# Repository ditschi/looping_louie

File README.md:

# Looping Louie Wi-Fi upgrade

Retrofit electronics for **Looping Louie** (old and new edition) and **Loopin' Chewie**. The board goes into the
**battery compartment without soldering** and makes the game controllable from a **web UI on your phone**, with
game modes, custom modes, game master and player roles. The original lever keeps working as start/stop.

*Main board (46 × 14.1 mm, AA format, 4 layers): ESP32-C6 module on the left, motor driver and power path in the
middle, USB-C on the right. Rendered from the current KiCad layout (`just images`).*

| Exploded | Assembled |
|---|---|
|  |  |

*The real board (KiCad 3D export) in the 3D-printed AA sleeve: shell, two end caps, filament dowels (red). Nickel
strips from the bottom pads make the battery contacts. The board registers in the slots of the end caps; the
envelope check `just hull` confirms it stays inside the AA diameter.*

## Status

> 2026-11-11 · second version, nothing ordered yet. The main board is rev B (low-Iq LDO TPS7A2633 for 3.3 V),
> the design to order; rev A with the SPX3819 LDO is kept as a fallback under the Git tag `rev-a-spx3819`.

| Part | State |
|---|---|
| Concept | done ([hardware](docs/hardware-concept.md), [software](docs/software-concept.md), [web UI](docs/web-ui-concept.md)) |
| Main board | schematic done, routed (own router), ERC/DRC 0, 0 unconnected; rev B with the LDO TPS7A2633 (VSYS 3.0–6.6 V, standby approx. 15–18 µA), datasheet delta review done ([main-board-c6.md](docs/main-board-c6.md)) |
| Charger board | schematic and layout done, ERC/DRC clean ([charger-board.md](docs/charger-board.md)) |
| 3D-printed parts | AA sleeve, C-cell adapter and charger holder modelled; checked against the current layout (`just hull`) |
| Firmware | Rust, step 0 written (bring-up and test probes), builds, not yet run on a board ([firmware/louie-fw](firmware/louie-fw/README.md)) |
| Web UI | clickable prototype ([web/poc](web/poc/README.md)) |

The old MicroPython/ESP8266 version is in the tag `v1-legacy`.

## Components

| Assembly | Description |
|---|---|
| **Main board** | AA cell format, 4 layers, components on one side: ESP32-C6-MINI-1 (Wi-Fi, BLE), DRV8213 H-bridge with current sensing, USB-C for flashing and 5 V operation, supply for 1S Li-ion up to 4 × AA, lever detection; solder pads on the bottom for player inputs, LEDs, I²C |
| **Charger board** | also AA format: USB-C (charging), charge controller, LiPo connection. Sits upright in the second compartment (replaces the bridge there) or is glued into the base |
| **Bridge** | copper AA dummy for the second compartment when the charger board sits in the base |
| **AA sleeve / C-cell adapter** | 3D-printed shell with end caps that holds the main board in the AA compartment; an extra sleeve makes it fit the C-cell compartment of the old Louie ([hardware/mechanics](hardware/mechanics/README.md)) |
| **Firmware** | Rust (std on ESP-IDF); game logic as a hardware-independent crate that runs on the ESP, in PC tests and as WebAssembly in the browser (mode preview) |
| **Web UI** | served offline by the ESP; concept and clickable prototype in `web/poc` |

## Documentation

- Hardware: [hardware concept](docs/hardware-concept.md), [main board](docs/main-board-c6.md),
  [charger board](docs/charger-board.md) (with wiring diagram), [3D-printed parts](hardware/mechanics/README.md)
- Software: [firmware architecture](docs/firmware-architecture.md), [software concept](docs/software-concept.md),
  [web UI concept](docs/web-ui-concept.md), [mode builder](docs/mode-builder.md), [device pairing](docs/device-pairing.md)
- Test setup before the board exists: [test hardware](docs/test-hardware.md)
- Development workflow (tools, generators, router, routing score): [development](docs/development.md),
  [routing score](docs/routing-score.md), [code health](docs/code-health.md) (score, commit gate, hardware checks)
- Open items and decisions: [open items](docs/open-items.md), [decision history](docs/decision-history.md),
  [concept review 2026-11-10](docs/review-2026-11-10.md), [supply proposal: buck converter](docs/proposal-supply-buck.md),
  [supply proposal: standby with Li-ion](docs/proposal-supply-standby.md),
  [wiring review](docs/wiring-review.md)
- Costs: [cost estimate](docs/cost-estimate.md)
- Ideas and studies: [ideas](docs/ideas.md), [optional hardware](docs/idea-optional-hardware.md),
  [wireless buttons](docs/idea-wireless-buttons.md), [power bank](docs/idea-power-bank.md),
  [Zigbee](docs/idea-zigbee-operation.md), [wireless controllers](docs/analysis-wireless-controllers.md)

## Directories

```
docs/                 concepts, decisions, development guide, images (docs/images/)
hardware/
  bom/parts.csv       BOM with manufacturer parts, LCSC numbers, alternatives
  lib/                project library (symbols, footprints, 3D models) – created with just parts
  main-board/         KiCad project of the main board (4 layers)
  charger-board/      KiCad project of the charger board (2 layers)
  mechanics/          3D-printed parts (OpenSCAD): main board sleeve, charger board holder
  scripts/            generators (schematic, layout, placement), router with keep-best gate,
                      routing score, envelope check, part fetching, tool check
  routing-score.toml  weights of the routing score
web/
  poc/                clickable web UI prototype (one HTML file, offline)
  prototype/          first, outdated UI draft
firmware/louie-fw/    Rust firmware (ESP-IDF), step 0: bring-up and test probes
tools/                downloaded tools (Freerouting, pre-router), created by setup.sh, not in Git
AGENTS.md             orientation and validation for coding agents
justfile              all development commands (just --list)
setup.sh              installs all tools
```

## Quick start

```bash
./setup.sh     # install all tools (once, Ubuntu/Debian)
just check     # check the tools
just --list    # all commands
```

Common commands:

```bash
just images    # board renders, copper layers, schematic, sleeve assembly → docs/images/
just model     # 3D model of the board (STEP, GLB, STL) → build/main-board/3d/
just hull      # check the board against the AA sleeve
just stl       # 3D-print files and previews → build/mechanics/
just fab       # Gerber, drill, CPL and BOM for fabrication → build/main-board/fab/
```

Setup and workflow in detail: [docs/development.md](docs/development.md)

## License

Using, building and adapting the project is free for **non-commercial purposes**; making money with the project
requires prior permission. Software: [PolyForm Noncommercial 1.0.0](LICENSES/PolyForm-Noncommercial-1.0.0.md),
hardware and docs: [CC BY-NC-SA 4.0](LICENSES/CC-BY-NC-SA-4.0.txt). Details and exceptions: [LICENSE](LICENSE).

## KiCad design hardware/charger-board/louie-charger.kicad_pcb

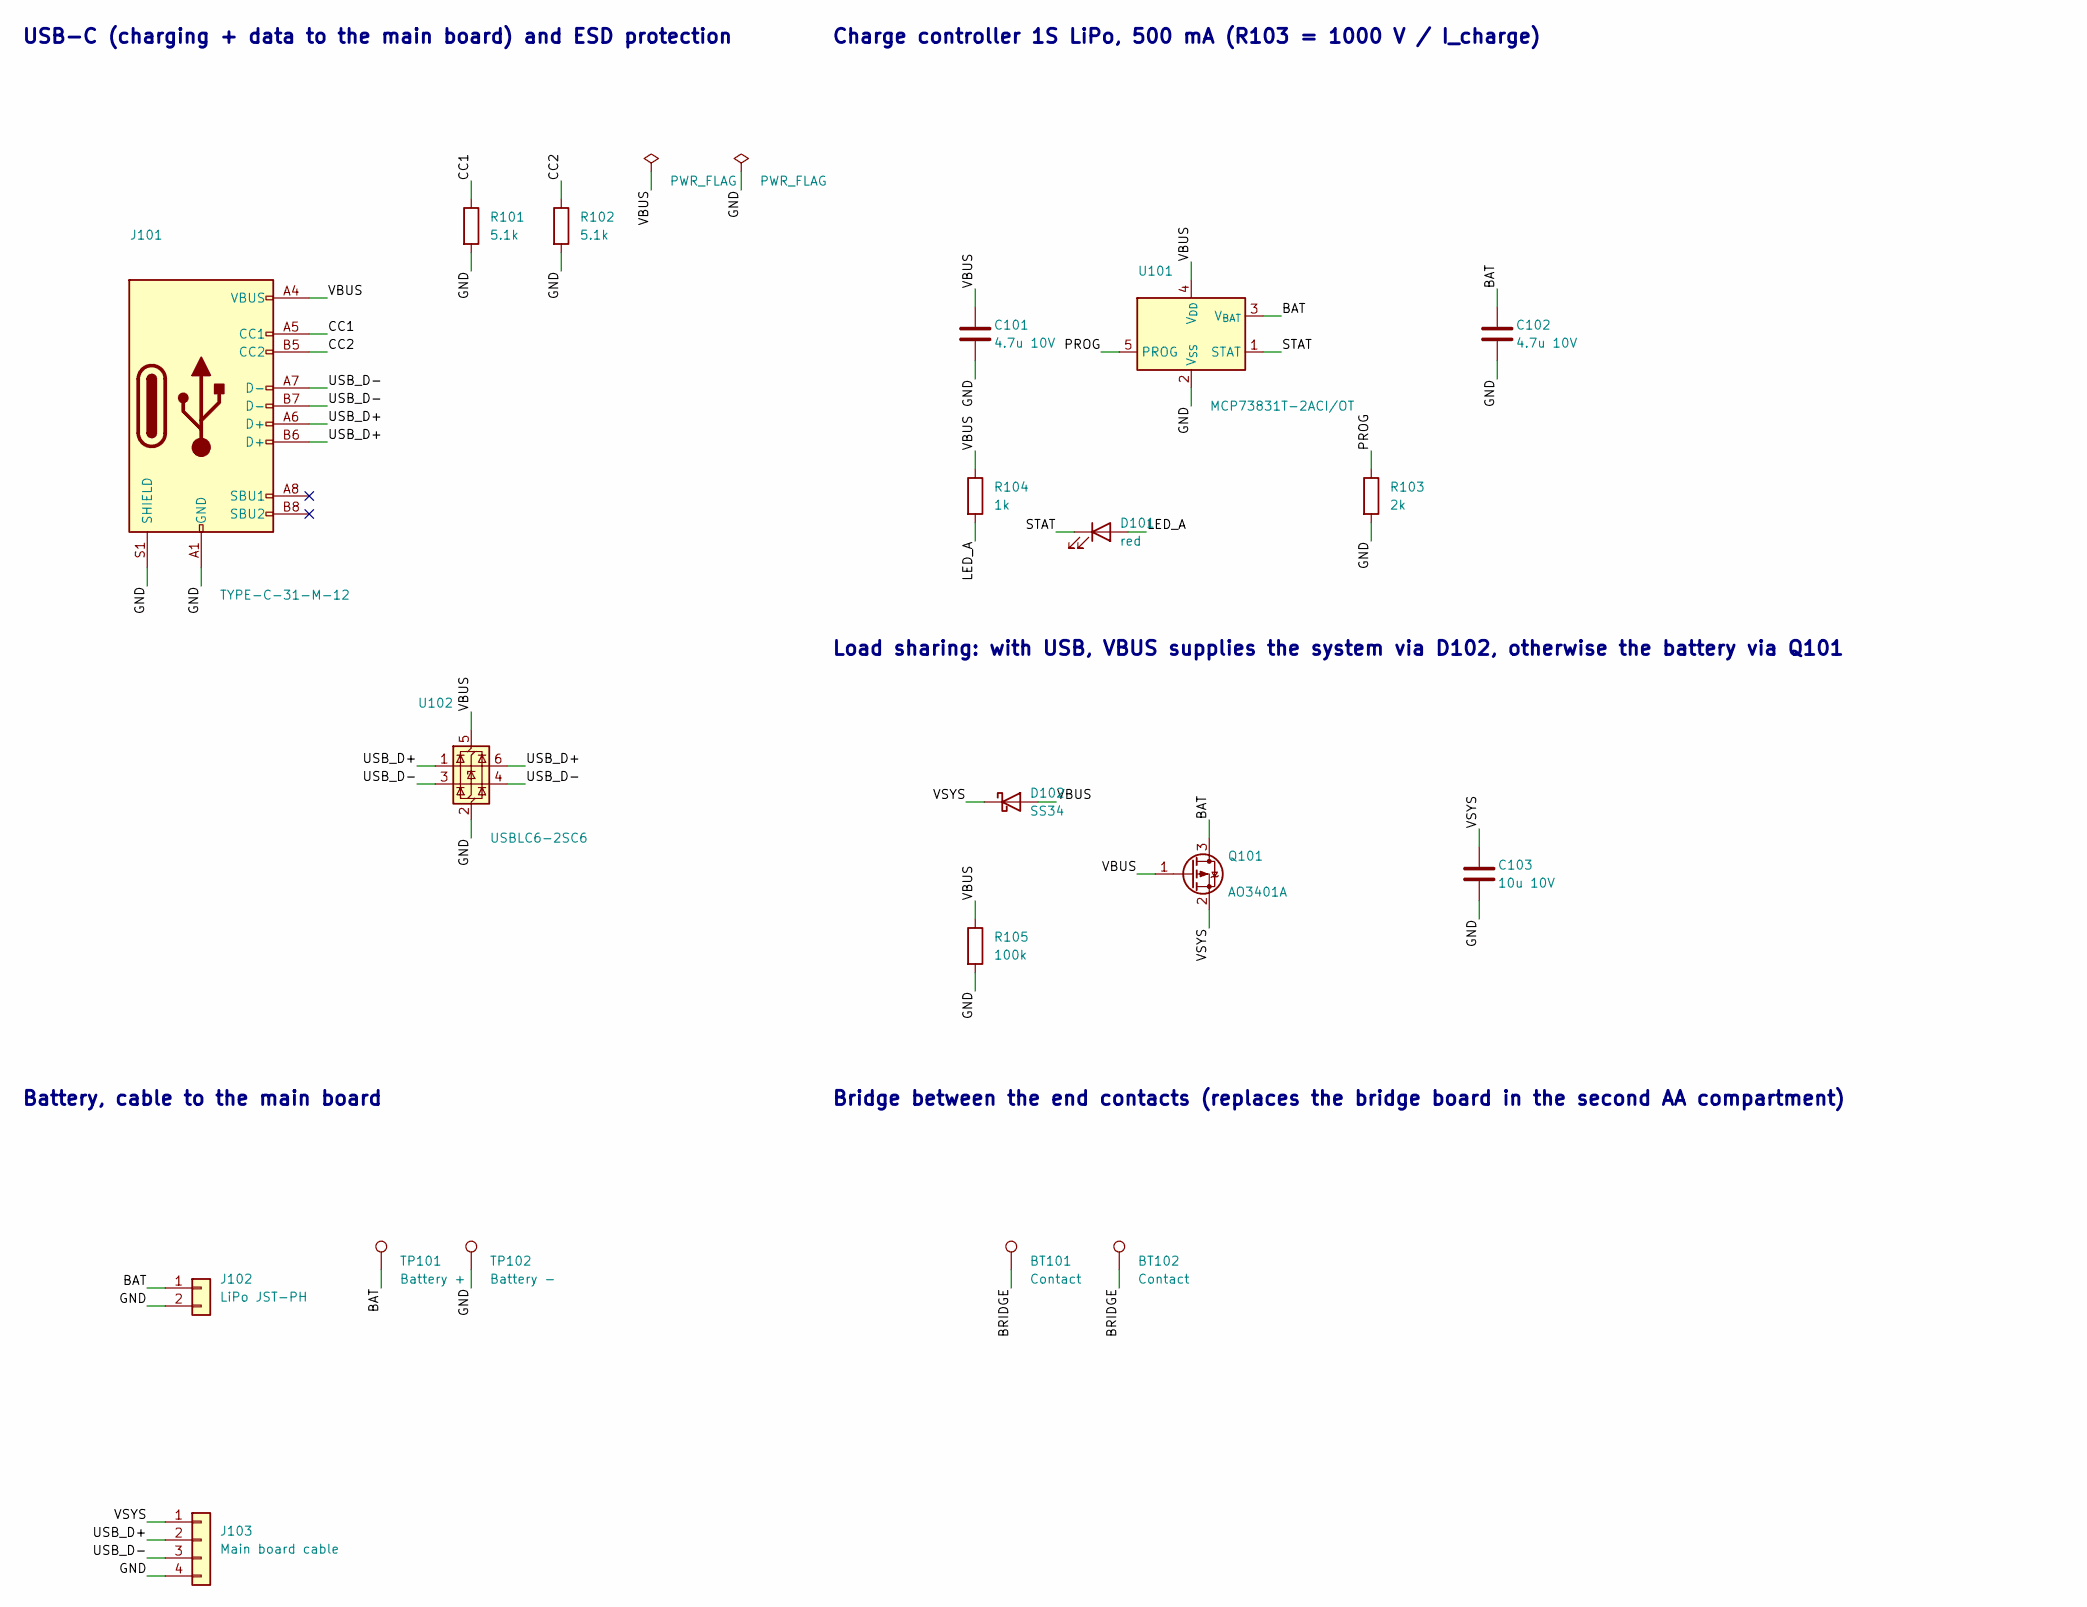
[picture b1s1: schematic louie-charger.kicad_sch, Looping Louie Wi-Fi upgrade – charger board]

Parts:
BT101, BT102: Contact; TestPoint_Pad_2.0x2.0mm
C101, C102: 4.7u 10V; C_0603_1608Metric
C103: 10u 10V; C_0805_2012Metric
D101: red; LED_0603_1608Metric; LCSC Part C2286
D102: SS34; D_SMA; LCSC Part C8678
J101: TYPE-C-31-M-12; USB_C_Receptacle_HRO_TYPE-C-31-M-12; LCSC Part C165948
J102: LiPo JST-PH; JST_PH_S2B-PH-SM4-TB_1x02-1MP_P2.00mm_Horizontal; LCSC Part C295747
J103: Main board cable; SolderPads_1x04_P2.00mm
Q101: AO3401A; SOT-23; LCSC Part C15127
R101, R102: 5.1k; R_0603_1608Metric
R103: 2k; R_0603_1608Metric
R104: 1k; R_0603_1608Metric
R105: 100k; R_0603_1608Metric
TP101: Battery +; TestPoint_Pad_2.0x2.0mm
TP102: Battery -; TestPoint_Pad_2.0x2.0mm
U101: MCP73831T-2ACI/OT; SOT-23-5; LCSC Part C424093
U102: USBLC6-2SC6; SOT-23-6; LCSC Part C7519

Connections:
/BAT: C102.1, J102.1, Q101.3 (D), TP101.1, U101.3 (V_{BAT})
/BRIDGE: BT101.1, BT102.1
/CC1: J101.A5 (CC1), R101.1
/CC2: J101.B5 (CC2), R102.1
/GND: C101.2, C102.2, C103.2, J101.A1 (GND), J101.A12 (GND), J101.B1 (GND), J101.B12 (GND), J101.S1 (SHIELD), J102.2, J103.4, R101.2, R102.2, R103.2, R105.2, TP102.1, U101.2 (V_{SS}), U102.2 (GND)
/LED_A: D101.2 (A), R104.2
/PROG: R103.1, U101.5 (PROG)
/STAT: D101.1 (K), U101.1 (STAT)
/USB_D+: J101.A6 (D+), J101.B6 (D+), J103.2, U102.1 (I/O1), U102.6 (I/O1)
/USB_D-: J101.A7 (D-), J101.B7 (D-), J103.3, U102.3 (I/O2), U102.4 (I/O2)
/VBUS: C101.1, D102.2 (A), J101.A4 (VBUS), J101.A9 (VBUS), J101.B4 (VBUS), J101.B9 (VBUS), Q101.1 (G), R104.1, R105.1, U101.4 (V_{DD}), U102.5 (VBUS)
/VSYS: C103.1, D102.1 (K), J103.1, Q101.2 (S)

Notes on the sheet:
USB-C (charging + data to the main board) and ESD protection
Charge controller 1S LiPo, 500 mA (R103 = 1000 V / I_charge)
Load sharing: with USB, VBUS supplies the system via D102, otherwise the battery via Q101
Battery, cable to the main board
Bridge between the end contacts (replaces the bridge board in the second AA compartment)

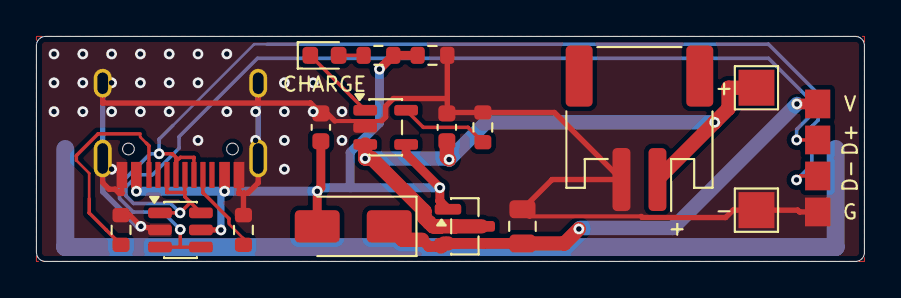
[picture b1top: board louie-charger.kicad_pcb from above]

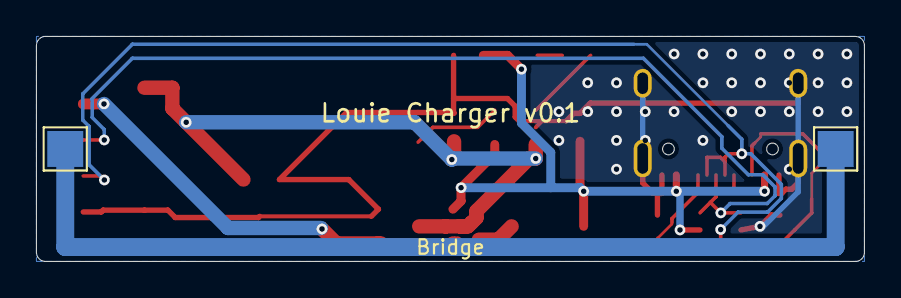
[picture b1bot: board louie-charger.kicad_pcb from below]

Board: 2 copper layers, 46.0 x 12.5 mm, 20 parts (2 on the bottom side), 12 nets.

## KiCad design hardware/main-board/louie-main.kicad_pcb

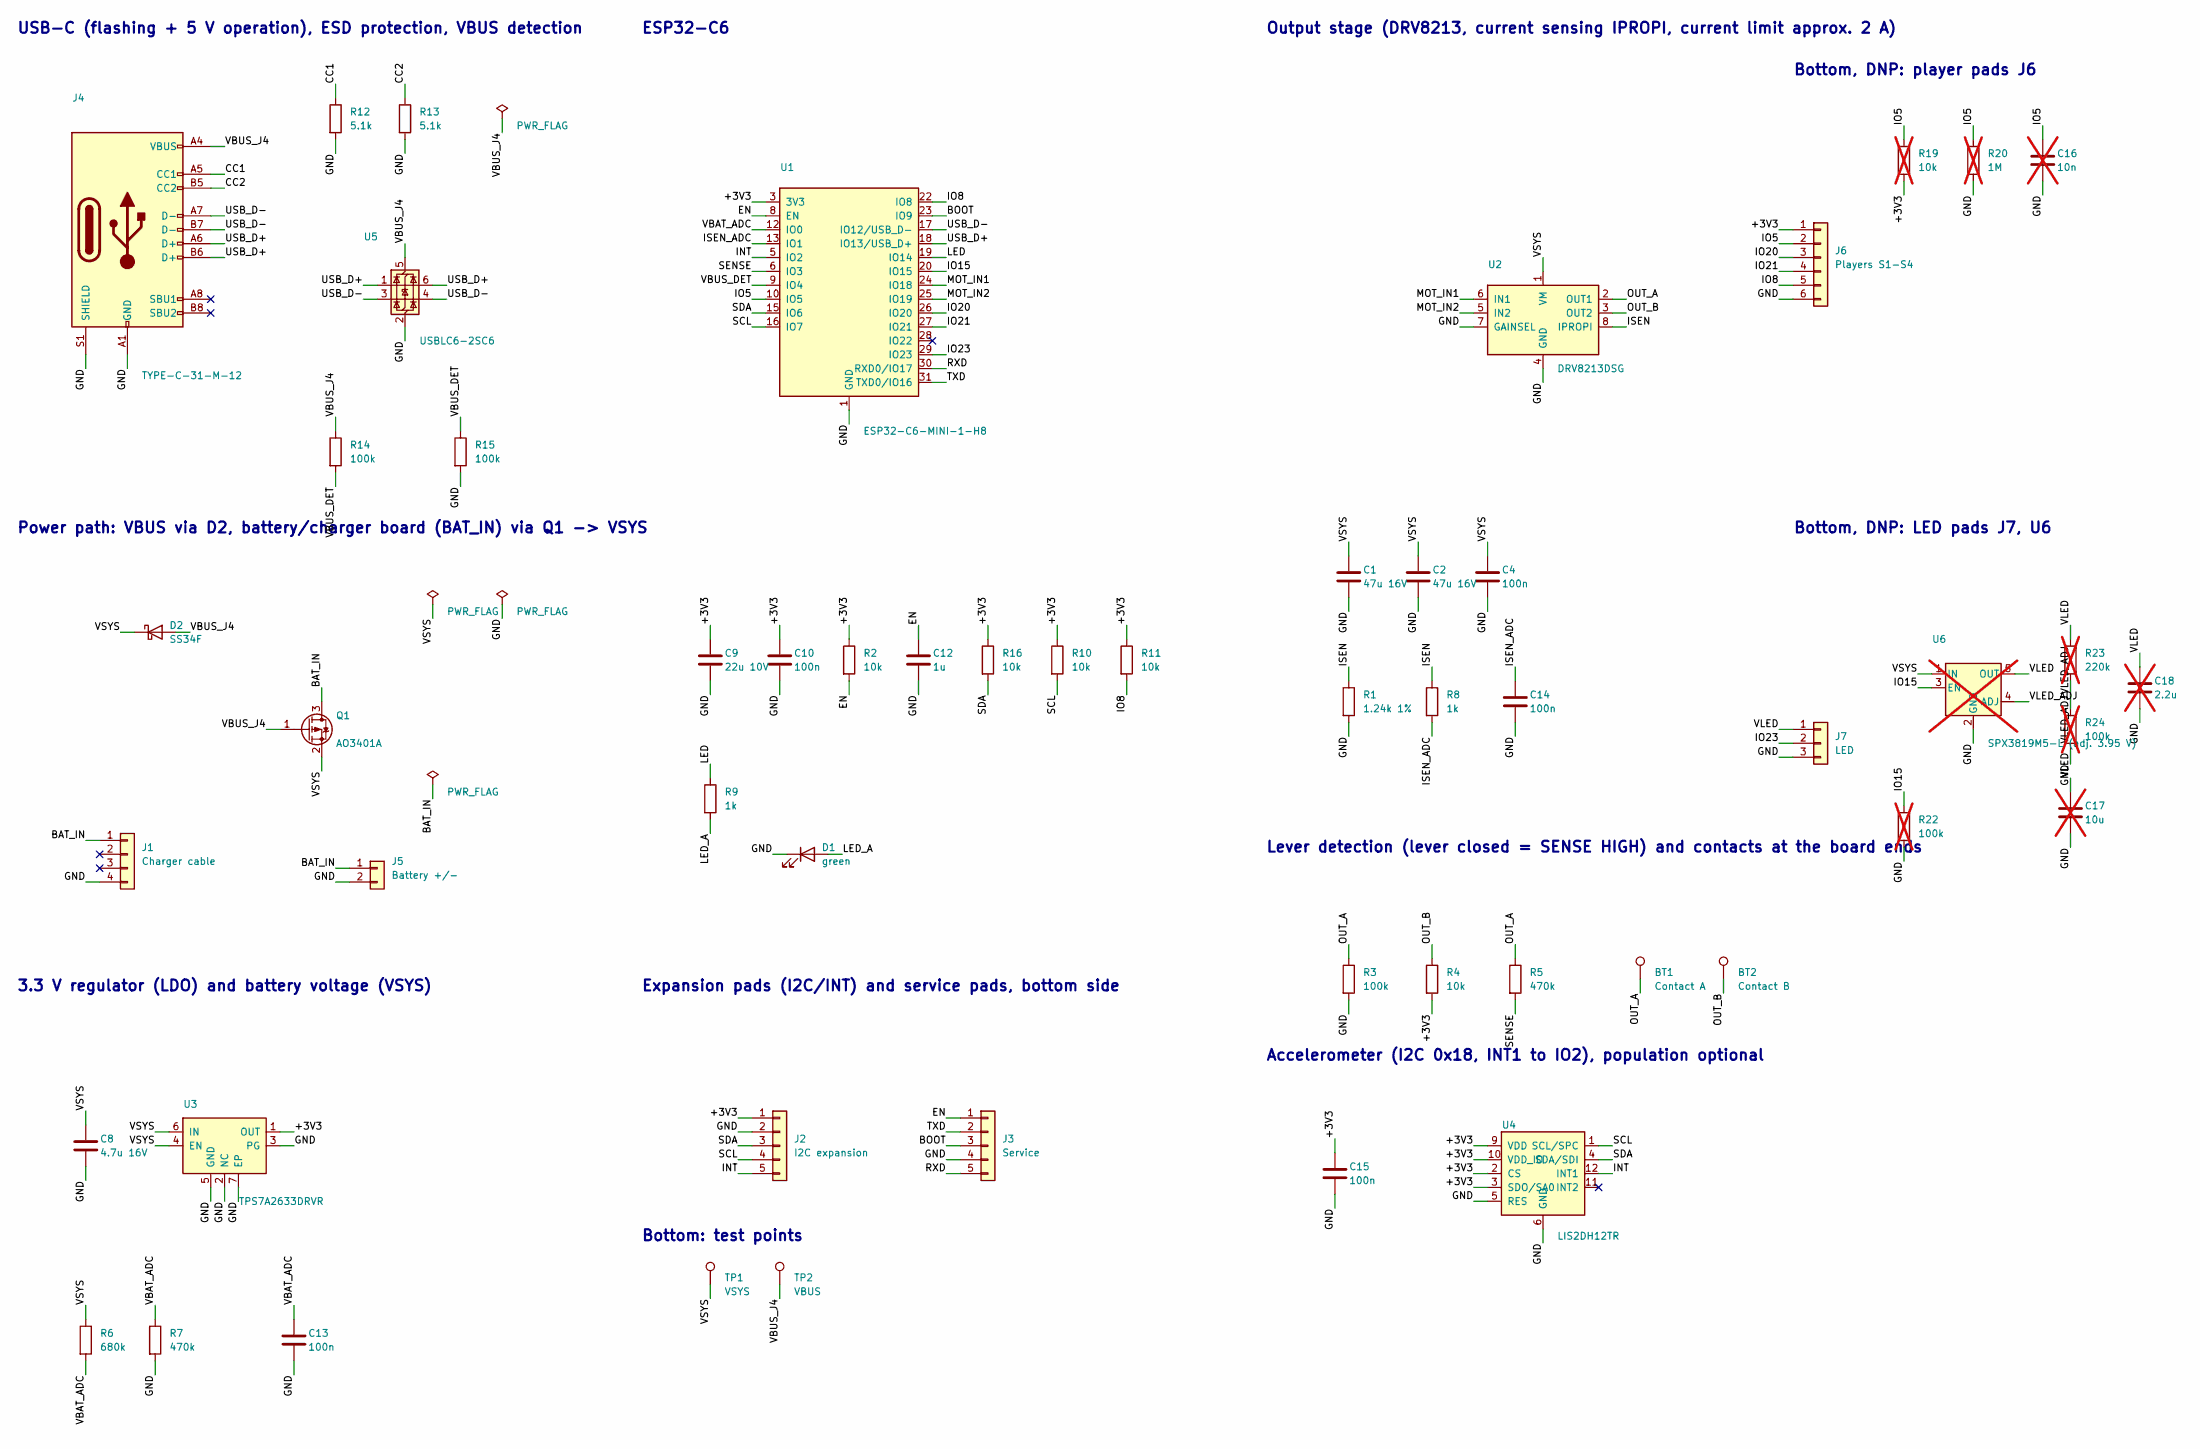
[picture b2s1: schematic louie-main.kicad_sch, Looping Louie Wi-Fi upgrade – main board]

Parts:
BT1: Contact A; TestPoint_Pad_2.0x2.0mm
BT2: Contact B; TestPoint_Pad_2.0x2.0mm
C1, C2: 47u 16V; C_1206_3216Metric
C4, C10, C13, C14, C15: 100n; C_0402_1005Metric
C8: 4.7u 16V; C_0402_1005Metric
C9: 22u 10V; C_0805_2012Metric
C12: 1u; C_0402_1005Metric
C16: 10n; C_0402_1005Metric; LCSC Part C15195; not fitted
C17: 10u; C_0805_2012Metric; LCSC Part C1713; not fitted
C18: 2.2u; C_0402_1005Metric; not fitted
D1: green; LED_0402_1005Metric
D2: SS34F; SMAF_L3.5-W2.6-LS4.7-RD; LCSC Part C60396
J1: Charger cable; SolderPads_1x04_P2.00mm
J2: I2C expansion; SolderPads_1x05_P2.54mm
J3: Service; SolderPads_1x05_P2.54mm
J4: TYPE-C-31-M-12; USB_C_Receptacle_HRO_TYPE-C-31-M-12; LCSC Part C165948
J5: Battery +/-; SolderPads_1x02_2.5x3.5mm
J6: Players S1-S4; SolderPads_1x06_P2.00mm
J7: LED; SolderPads_1x03_P2.54mm
Q1: AO3401A; SOT-23; LCSC Part C15127
R1: 1.24k 1%; R_0402_1005Metric
R2, R4, R10, R11, R16: 10k; R_0402_1005Metric
R3, R14, R15: 100k; R_0402_1005Metric
R5, R7: 470k; R_0402_1005Metric
R6: 680k; R_0402_1005Metric
R8, R9: 1k; R_0402_1005Metric
R12, R13: 5.1k; R_0402_1005Metric
R19: 10k; R_0402_1005Metric; LCSC Part C25744; not fitted
R20: 1M; R_0402_1005Metric; not fitted
R22: 100k; R_0402_1005Metric; LCSC Part C25741; not fitted
R23: 220k; R_0402_1005Metric; not fitted
R24: 100k; R_0402_1005Metric; not fitted
TP1: VSYS; TestPad_D1.0mm
TP2: VBUS; TestPad_D1.0mm
U1: ESP32-C6-MINI-1-H8; WIFIM-SMD_ESP32-C6-MINI-1; LCSC Part C42403058
U2: DRV8213DSG; WSON-8-1EP_2x2mm_P0.5mm_EP0.9x1.6mm; LCSC Part C22407186
U3: TPS7A2633DRVR; WSON-6-1EP_2x2mm_P0.65mm_EP1x1.6mm; LCSC Part C2876256
U4: LIS2DH12TR; LGA-12_2x2mm_P0.5mm; LCSC Part C110926
U5: USBLC6-2SC6; SOT-23-6; LCSC Part C7519
U6: SPX3819M5-L (adj. 3.95 V); SOT-23-5; not fitted

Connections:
/+3V3: C9.1, C10.1, C15.1, J2.1, J6.1, R2.1, R4.2, R10.1, R11.1, R16.1, R19.2, U1.3 (3V3), U3.1 (OUT), U4.2 (CS), U4.3 (SDO/SA0), U4.9 (VDD), U4.10 (VDD_IO)
/BAT_IN: J1.1, J5.1, Q1.3 (D)
/BOOT: J3.3, U1.23 (IO9)
/CC1: J4.A5 (CC1), R12.1
/CC2: J4.B5 (CC2), R13.1
/EN: C12.1, J3.1, R2.2, U1.8 (EN)
/GND: C1.2, C2.2, C4.2, C8.2, C9.2, C10.2, C12.2, C13.2, C14.2, C15.2, C16.2, C17.2, C18.2, D1.1 (K), J1.4, J2.2, J3.4, J4.A1 (GND), J4.A12 (GND), J4.B1 (GND), J4.B12 (GND), J4.S1 (SHIELD), J5.2, J6.6, J7.3, R1.2, R3.2, R7.2, R12.2, R13.2, R15.2, R20.2, R22.2, R24.2, U1.1 (GND), U1.2 (GND), U1.11 (GND), U1.14 (GND), U1.36 (GND), U1.37 (GND), U1.38 (GND), U1.39 (GND), U1.40 (GND), U1.41 (GND), U1.42 (GND), U1.43 (GND), U1.44 (GND), U1.45 (GND), U1.46 (GND), U1.47 (GND), U1.48 (GND), U1.49 (GND), U1.50 (GND), U1.51 (GND), U1.52 (GND), U1.53 (GND), U2.4 (GND), U2.7 (GAINSEL), U2.9 (GND), U3.2 (NC), U3.3 (PG), U3.5 (GND), U3.7 (EP), U4.5 (RES), U4.6 (GND), U4.7 (GND), U4.8 (GND), U5.2 (GND), U6.2 (GND)
/INT: J2.5, U1.5 (IO2), U4.12 (INT1)
/IO5: C16.1, J6.2, R19.1, R20.1, U1.10 (IO5)
/IO8: J6.5, R11.2, U1.22 (IO8)
/IO15: R22.1, U1.20 (IO15), U6.3 (EN)
/IO20: J6.3, U1.26 (IO20)
/IO21: J6.4, U1.27 (IO21)
/IO23: J7.2, U1.29 (IO23)
/ISEN: R1.1, R8.1, U2.8 (IPROPI)
/ISEN_ADC: C14.1, R8.2, U1.13 (IO1)
/LED: R9.1, U1.19 (IO14)
/LED_A: D1.2 (A), R9.2
/MOT_IN1: U1.24 (IO18), U2.6 (IN1)
/MOT_IN2: U1.25 (IO19), U2.5 (IN2)
/OUT_A: BT1.1, R3.1, R5.1, U2.2 (OUT1)
/OUT_B: BT2.1, R4.1, U2.3 (OUT2)
/RXD: J3.5, U1.30 (RXD0/IO17)
/SCL: J2.4, R10.2, U1.16 (IO7), U4.1 (SCL/SPC)
/SDA: J2.3, R16.2, U1.15 (IO6), U4.4 (SDA/SDI)
/SENSE: R5.2, U1.6 (IO3)
/TXD: J3.2, U1.31 (TXD0/IO16)
/USB_D+: J4.A6 (D+), J4.B6 (D+), U1.18 (IO13/USB_D+), U5.1 (I/O1), U5.6 (I/O1)
/USB_D-: J4.A7 (D-), J4.B7 (D-), U1.17 (IO12/USB_D-), U5.3 (I/O2), U5.4 (I/O2)
/VBAT_ADC: C13.1, R6.2, R7.1, U1.12 (IO0)
/VBUS_DET: R14.2, R15.1, U1.9 (IO4)
/VBUS_J4: D2.2 (A), J4.A4 (VBUS), J4.A9 (VBUS), J4.B4 (VBUS), J4.B9 (VBUS), Q1.1 (G), R14.1, TP2.1, U5.5 (VBUS)
/VLED: C17.1, C18.1, J7.1, R23.1, U6.5 (OUT)
/VLED_ADJ: R23.2, R24.1, U6.4 (ADJ)
/VSYS: C1.1, C2.1, C4.1, C8.1, D2.1 (K), Q1.2 (S), R6.1, TP1.1, U2.1 (VM), U3.4 (EN), U3.6 (IN), U6.1 (IN)

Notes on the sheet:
USB-C (flashing + 5 V operation), ESD protection, VBUS detection
Power path: VBUS via D2, battery/charger board (BAT_IN) via Q1 -> VSYS
3.3 V regulator (LDO) and battery voltage (VSYS)
ESP32-C6
Output stage (DRV8213, current sensing IPROPI, current limit approx. 2 A)
Lever detection (lever closed = SENSE HIGH) and contacts at the board ends
Expansion pads (I2C/INT) and service pads, bottom side
Accelerometer (I2C 0x18, INT1 to IO2), population optional
Bottom, DNP: player pads J6
Bottom, DNP: LED pads J7, U6
Bottom: test points

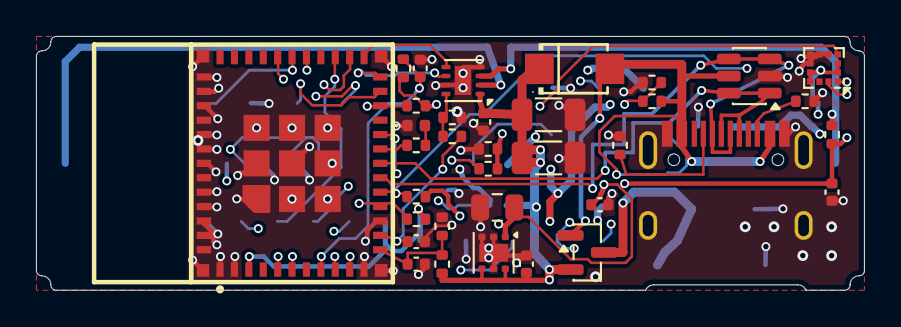
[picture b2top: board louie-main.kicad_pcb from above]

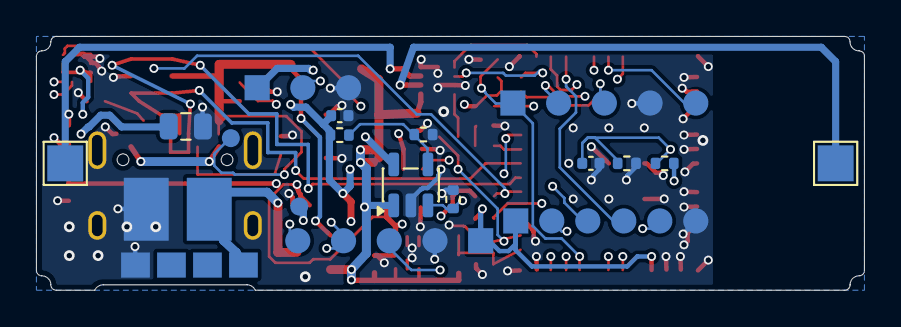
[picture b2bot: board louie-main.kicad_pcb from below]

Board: 4 copper layers, 46.0 x 14.1 mm, 54 parts (19 on the bottom side), 35 nets.

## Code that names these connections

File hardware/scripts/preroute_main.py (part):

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
def preroute_supply(board, fps):
    """VSYS main track in advance (0.5 mm): cathode of Schottky D2 -> C1 -> C2 (vertical at the left
    pads), branch C1 -> C4 -> VM pin 1 of the DRV8213. The rest of VSYS (Q1, LDO, divider) and BAT_IN/VBUS
    are routed by Freerouting in the Power net class."""

    def at(ref, num):
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

def preroute_outputs(board, driver, contact_a, contact_b):
    """Outputs of the DRV8213 in advance: OUT1 (pin 2, OUT_A) and OUT2 (pin 3, OUT_B) each with a 0.3 mm stub to a
    via, on the bottom with 0.4 mm along the -y edge: OUT_A to the left under module and antenna (edge strip) to
    end contact BT1, OUT_B to the right to end contact BT2. Expects rotation 180° (pins 1–4 point to +x)."""
    assert round(driver.GetOrientationDegrees()) % 360 == 180, "preroute_outputs expects rotation 180°"
    pa, pb = pad_of(driver, "2").GetPosition(), pad_of(driver, "3").GetPosition()
    out_a, out_b = pad_of(driver, "2").GetNet(), pad_of(driver, "3").GetNet()
    edge_y = mm(ORIGIN[1] - EDGE_TRACK_Y)
    # OUT_A: via right of the pin, on the bottom diagonally under the driver to the edge, then to the left
    va = (pa.x + mm(1.15), pa.y)
    add_track(board, out_a, (pcbnew.F_Cu, STUB_TRACK), (pa.x, pa.y), va)
    add_via(board, out_a, *va)
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        (ca.x, edge_y + mm(0.8)),
        (ca.x, ca.y),
    )
    # OUT_B: stub diagonally to the lower right (past GND pin 4), via, on the bottom along the edge to the right
    vb = (pb.x + mm(1.7), pb.y - mm(0.4))
    add_track(
        board, out_b, (pcbnew.F_Cu, STUB_TRACK), (pb.x, pb.y), (pb.x + mm(0.6), pb.y), (pb.x + mm(1.0), vb[1]), vb
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

def preroute_led_ldo(board, fps):
    """LED LDO U6 (bottom, DNP): VIN (pin 1) with 0.4 mm on B.Cu straight to the battery VSYS track at x = 4.67, which
    runs 1.5 mm to its right; route_fix.py did not find this short path (variant test 2026-11-10)."""
    pad = pad_of(fps["U6"], "1")
    q = pad.GetPosition()
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def preroute_adc_stubs(board, fps):
    """Short analog connections at the right module pins, locked so that no fanout via or foreign track takes the
    0.7 mm gap between the module pads and the 0402 row (variant test 2026-11-08, docs/main-board-c6.md 11):
    pad 12 (VBAT_ADC) -> C13, pad 13 (ISEN_ADC) -> C14, C13 -> R6 pin 2 above C13 pin 2 (GND), R6 pin 2 -> R7 pin 1.
    Replaces the former VBAT_ADC escape via at the old R6 place."""

    def q(ref, num):
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
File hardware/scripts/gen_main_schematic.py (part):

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        # Flow-through (ST DS4260 Rev 5, Fig. 1/7/18): I/O1 = pins 1 and 6, I/O2 = pins 3 and 4 are each
        # the same node. The line comes from J4 to pin 1/3 and continues under the package to pin 6/4
        # towards the module (no branch/stub).
        pins={"1": "USB_D+", "6": "USB_D+", "3": "USB_D-", "4": "USB_D-", "5": "VBUS_J4", "2": "GND"},
    ),
    # VBUS_DET: divider 100k/100k to IO4 (5 V -> 2.5 V), also gate pull-down of Q1, discharges VBUS
    R("R14", "100k", ("VBUS_J4", "VBUS_DET"), at=(83.82, 101.6)),
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        lcsc="C60396",
        fp="lcsc:SMAF_L3.5-W2.6-LS4.7-RD",
        at=(50.8, 134.62),
        pins={"2": "VBUS_J4", "1": "VSYS"},
    ),
    # Gate to VBUS: with USB, Q1 blocks (no charging of the cell from VBUS), without USB it conducts (gate via
    # R14+R15 to GND). Body diode BAT_IN -> VSYS; cell reversed -> Q1 blocks (reverse polarity protection).
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        at=(78.74, 152.4),
        ref_at=(5.08, -2.54),
        val_at=(5.08, 2.54),
        pins={"1": "VBUS_J4", "2": "VSYS", "3": "BAT_IN"},
    ),
    # Bottom side: cable to the charger board (1 BAT_IN, 4 GND; 2/3 free) and battery pads (cell direct)
    dict(
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        fp="louie:SolderPads_1x04_P2.00mm",
        bom=False,  # solder pads for stranded wires, not populated
        # Only BAT_IN and GND: flashing exclusively via J4 (client decision). Pads 2/3 stay without
        # a net so that the cable pinout of charger board v0.1 (1 VSYS, 2 D+, 3 D-, 4 GND) fits
        at=(45.72, 175.26),
        pins={"1": "BAT_IN", "4": "GND"},
    ),
    dict(
        ref="J5",
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        fp="louie:SolderPads_1x02_2.5x3.5mm",
        bom=False,
        at=(91.44, 177.8),
        pins={"1": "BAT_IN", "2": "GND"},
    ),
    FLAG(1, "VSYS", (101.6, 129.54)),
    FLAG(2, "GND", (114.3, 129.54)),
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        at=(63.5, 228.6),
        ref_at=(-7.62, -7.62),
        val_at=(2.54, 10.16),
        pins={"6": "VSYS", "4": "VSYS", "1": "+3V3", "3": "GND", "5": "GND", "2": "GND", "7": "GND"},
    ),
    C("C8", "4.7u 16V", ("VSYS", "GND"), at=(38.1, 228.6)),
    # --- Battery voltage: 680k/470k, VSYS up to 6.6 V (4 x AA fresh) -> 2.7 V (C6 ADC up to 3.3 V) --------
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        value="green",
        fp="LED_SMD:LED_0402_1005Metric",
        at=(170.18, 175.26),
        pins={"2": "LED_A", "1": "GND"},
    ),
    # Bottom side: solder pads at 2.54 mm pitch (pin header/cable), not populated
    dict(
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        bom=False,
        fp="louie:SolderPads_1x03_P2.54mm",
        at=(355.6, 154.94),
        pins={"1": "VLED", "2": "IO23", "3": "GND"},
    ),
    # SPX3819 adjustable (EN V_IH 2.0 V): VOUT = 1.235 V × (1 + R23/R24) = 3.95 V. At 3.95 V the V5 LED types need
    # V_IH 0.63 × 3.95 = 2.49 V, below the guaranteed ESP32 V_OH (2.64 V); at 5.0 V (3.15 V) the 3.3 V data line
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            at=(383.54, 144.78),
            ref_at=(-7.62, -8.89),
            val_at=(2.54, 10.16),
            pins={"1": "VSYS", "2": "GND", "3": "IO15", "4": "VLED_ADJ", "5": "VLED"},
        )
    ),
    DNP(R("R23", "220k", ("VLED", "VLED_ADJ"), at=(401.32, 139.7))),
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
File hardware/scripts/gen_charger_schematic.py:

#!/usr/bin/env python3
"""Generates the charger board schematic from the circuit description below.

The charger board has the format of the main board (AA) and replaces the bridge in the second AA compartment:
USB-C (horizontal, the plug comes from above across the cell axis), charge controller MCP73831 with load sharing
(play while charging), ESD protection, charge indicator, battery connection, cable solder pads to the main board and
a copper bridge between the end contacts. Alternatively it is glued into the base.

Usage (via just):  just charger-schematic

Warning: overwrites hardware/charger-board/louie-charger.kicad_sch.
"""

import gen_main_schematic as base
from gen_main_schematic import FLAG, TP, TP_CONTACT, C, R

SCH = base.HARDWARE / "charger-board" / "louie-charger.kicad_sch"
R0603 = "Resistor_SMD:R_0603_1608Metric"
C0603 = "Capacitor_SMD:C_0603_1608Metric"
C0805 = "Capacitor_SMD:C_0805_2012Metric"


def R6(*args, **extra):
    return R(*args, fp=R0603, **extra)


BLOCKS = [
    ("USB-C (charging + data to the main board) and ESD protection", (25.4, 25.4)),
    ("Charge controller 1S LiPo, 500 mA (R103 = 1000 V / I_charge)", (139.7, 25.4)),
    ("Load sharing: with USB, VBUS supplies the system via D102, otherwise the battery via Q101", (139.7, 111.76)),
    ("Battery, cable to the main board", (25.4, 175.26)),
    ("Bridge between the end contacts (replaces the bridge board in the second AA compartment)", (139.7, 175.26)),
]

PARTS = [
    # --- USB-C ---------------------------------------------------------------------------------
    dict(
        ref="J101",
        lib="Connector:USB_C_Receptacle_USB2.0_16P",
        value="TYPE-C-31-M-12",
        lcsc="C165948",
        fp="Connector_USB:USB_C_Receptacle_HRO_TYPE-C-31-M-12",
        at=(50.8, 76.2),
        ref_at=(-10.16, -24.13),
        val_at=(2.54, 26.67),
        pins={
            "A4": "VBUS",
            "A9": "VBUS",
            "B4": "VBUS",
            "B9": "VBUS",
            "A5": "CC1",
            "B5": "CC2",
            "A6": "USB_D+",
            "B6": "USB_D+",
            "A7": "USB_D-",
            "B7": "USB_D-",
            "A1": "GND",
            "A12": "GND",
            "B1": "GND",
            "B12": "GND",
            "S1": "GND",
        },
    ),
    # 5.1 k at CC1/CC2: device (sink), every USB-C power supply then delivers 5 V
    R6("R101", "5.1k", ("CC1", "GND"), at=(88.9, 50.8)),
    R6("R102", "5.1k", ("CC2", "GND"), at=(101.6, 50.8)),
    dict(
        ref="U102",
        lib="Power_Protection:USBLC6-2SC6",
        value="USBLC6-2SC6",
        lcsc="C7519",
        fp="Package_TO_SOT_SMD:SOT-23-6",
        at=(88.9, 127),
        ref_at=(-7.62, -8.89),
        val_at=(2.54, 10.16),
        pins={"1": "USB_D+", "6": "USB_D+", "3": "USB_D-", "4": "USB_D-", "5": "VBUS", "2": "GND"},
    ),
    FLAG(1, "VBUS", (114.3, 43.18)),
    FLAG(2, "GND", (127, 43.18)),
    # --- Charge controller ----------------------------------------------------------------------
    dict(
        ref="U101",
        lib="Battery_Management:MCP73831-2-OT",
        value="MCP73831T-2ACI/OT",
        lcsc="C424093",
        fp="Package_TO_SOT_SMD:SOT-23-5",
        at=(190.5, 66.04),
        ref_at=(-7.62, -8.89),
        val_at=(2.54, 10.16),
        pins={"4": "VBUS", "2": "GND", "3": "BAT", "5": "PROG", "1": "STAT"},
    ),
    C("C101", "4.7u 10V", ("VBUS", "GND"), at=(160.02, 66.04), fp=C0603),
    C("C102", "4.7u 10V", ("BAT", "GND"), at=(233.68, 66.04), fp=C0603),
    R6("R103", "2k", ("PROG", "GND"), at=(215.9, 88.9)),
    # charge indicator: STAT pulls to GND while charging -> LED on; full or without USB -> off
    R6("R104", "1k", ("VBUS", "LED_A"), at=(160.02, 88.9)),
    dict(
        ref="D101",
        lib="Device:LED",
        value="red",
        lcsc="C2286",
        fp="LED_SMD:LED_0603_1608Metric",
        at=(177.8, 93.98),
        pins={"2": "LED_A", "1": "STAT"},
    ),
    # --- Load sharing (Microchip AN1149) -------------------------------------------------------
    dict(
        ref="Q101",
        lib="Transistor_FET:AO3401A",
        value="AO3401A",
        lcsc="C15127",
        fp="Package_TO_SOT_SMD:SOT-23",
        at=(190.5, 142.24),
        ref_at=(5.08, -2.54),
        val_at=(5.08, 2.54),
        pins={"1": "VBUS", "2": "VSYS", "3": "BAT"},
    ),
    dict(
        ref="D102",
        lib="Device:D_Schottky",
        value="SS34",
        lcsc="C8678",
        fp="Diode_SMD:D_SMA",
        at=(165.1, 132.08),
        pins={"2": "VBUS", "1": "VSYS"},
    ),
    R6("R105", "100k", ("VBUS", "GND"), at=(160.02, 152.4)),  # pulls the gate to GND without USB -> Q101 conducts
    C("C103", "10u 10V", ("VSYS", "GND"), at=(231.14, 142.24), fp=C0805),
    # --- Battery and cable ---------------------------------------------------------------------
    dict(
        ref="J102",
        lib="Connector_Generic:Conn_01x02",
        value="LiPo JST-PH",
        lcsc="C295747",
        fp="Connector_JST:JST_PH_S2B-PH-SM4-TB_1x02-1MP_P2.00mm_Horizontal",
        at=(50.8, 200.66),
        pins={"1": "BAT", "2": "GND"},
    ),
    TP("TP101", "Battery +", "BAT", at=(76.2, 198.12), fp=TP_CONTACT),  # solder pads instead of connector
    TP("TP102", "Battery -", "GND", at=(88.9, 198.12), fp=TP_CONTACT),
    dict(
        ref="J103",
        lib="Connector_Generic:Conn_01x04",
        value="Main board cable",
        fp="louie:SolderPads_1x04_P2.00mm",
        bom=False,  # same pinout as J1 of the main board
        at=(50.8, 236.22),
        pins={"1": "VSYS", "2": "USB_D+", "3": "USB_D-", "4": "GND"},
    ),
    # --- Bridge --------------------------------------------------------------------------------
    TP("BT101", "Contact", "BRIDGE", at=(165.1, 198.12), fp=TP_CONTACT),
    TP("BT102", "Contact", "BRIDGE", at=(180.34, 198.12), fp=TP_CONTACT),
]


if __name__ == "__main__":
    base.main(
        base.Sheet(
            path=SCH,
            parts=PARTS,
            blocks=BLOCKS,
            title="Looping Louie Wi-Fi upgrade – charger board",
            comment="AA format (compartment 2 instead of the bridge) or glued into the base, see docs/charger-board.md",
            project="louie-charger",
            generator="gen_charger_schematic.py",
        )
    )

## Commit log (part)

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2018-09-30 Added startup script boot.py
2018-09-30 initial main.py allowing to control the onboard LED
2021-10-03 current unstaged work
2021-10-03 wip -- reworked game and hw_control
2023-02-10 current work before switching to esp32 config
2023-02-10 boot.py now working - hardware/Led.py - hardware/wifi.py
2023-02-13 Timers, LED and morotr abstraction now working
2023-02-13 Timers, LED and motor abstraction now working
2023-02-13 added Fritzing pcb
2023-11-07 Bump flake8 from 6.0.0 to 6.1.0
    Bumps [flake8](https://github.com/pycqa/flake8) from 6.0.0 to 6.1.0.
    - [Commits](https://github.com/pycqa/flake8/compare/6.0.0...6.1.0)
    ---
    updated-dependencies:
    - dependency-name: flake8
    dependency-type: direct:development
2023-11-07 current work
2023-11-07 updating pipenv
2023-11-13 Bump black from 22.12.0 to 23.11.0
    Bumps [black](https://github.com/psf/black) from 22.12.0 to 23.11.0.
    - [Release notes](https://github.com/psf/black/releases)
    - [Changelog](https://github.com/psf/black/blob/main/CHANGES.md)
    - [Commits](https://github.com/psf/black/compare/22.12.0...23.11.0)
    ---
    updated-dependencies:
2023-11-13 Bump gitpython from 3.1.31 to 3.1.37
    Bumps [gitpython](https://github.com/gitpython-developers/GitPython) from 3.1.31 to 3.1.37.
    - [Release notes](https://github.com/gitpython-developers/GitPython/releases)
    - [Changelog](https://github.com/gitpython-developers/GitPython/blob/main/CHANGES)
    - [Commits](https://github.com/gitpython-developers/GitPython/compare/3.1.31...3.1.37)
    ---
    updated-dependencies:
2023-11-29 Bump cryptography from 41.0.5 to 41.0.6
    Bumps [cryptography](https://github.com/pyca/cryptography) from 41.0.5 to 41.0.6.
    - [Changelog](https://github.com/pyca/cryptography/blob/main/CHANGELOG.rst)
    - [Commits](https://github.com/pyca/cryptography/compare/41.0.5...41.0.6)
    ---
    updated-dependencies:
    - dependency-name: cryptography
2023-12-11 Bump pylint from 3.0.2 to 3.0.3
    Bumps [pylint](https://github.com/pylint-dev/pylint) from 3.0.2 to 3.0.3.
    - [Release notes](https://github.com/pylint-dev/pylint/releases)
    - [Commits](https://github.com/pylint-dev/pylint/compare/v3.0.2...v3.0.3)
    ---
    updated-dependencies:
    - dependency-name: pylint
2023-12-18 Bump black from 23.11.0 to 23.12.0
    Bumps [black](https://github.com/psf/black) from 23.11.0 to 23.12.0.
    - [Release notes](https://github.com/psf/black/releases)
    - [Changelog](https://github.com/psf/black/blob/main/CHANGES.md)
    - [Commits](https://github.com/psf/black/compare/23.11.0...23.12.0)
    ---
    updated-dependencies:
2023-12-25 Bump black from 23.11.0 to 23.12.1
    Bumps [black](https://github.com/psf/black) from 23.11.0 to 23.12.1.
    - [Release notes](https://github.com/psf/black/releases)
    - [Changelog](https://github.com/psf/black/blob/main/CHANGES.md)
    - [Commits](https://github.com/psf/black/compare/23.11.0...23.12.1)
    ---
    updated-dependencies:
2024-01-01 Bump pytest from 7.4.3 to 7.4.4
    Bumps [pytest](https://github.com/pytest-dev/pytest) from 7.4.3 to 7.4.4.
    - [Release notes](https://github.com/pytest-dev/pytest/releases)
    - [Changelog](https://github.com/pytest-dev/pytest/blob/main/CHANGELOG.rst)
    - [Commits](https://github.com/pytest-dev/pytest/compare/7.4.3...7.4.4)
    ---
    updated-dependencies:
2024-01-08 Bump flake8 from 6.1.0 to 7.0.0
    Bumps [flake8](https://github.com/pycqa/flake8) from 6.1.0 to 7.0.0.
    - [Commits](https://github.com/pycqa/flake8/compare/6.1.0...7.0.0)
    ---
    updated-dependencies:
    - dependency-name: flake8
    dependency-type: direct:development
2024-01-10 Bump gitpython from 3.1.37 to 3.1.41
    Bumps [gitpython](https://github.com/gitpython-developers/GitPython) from 3.1.37 to 3.1.41.
    - [Release notes](https://github.com/gitpython-developers/GitPython/releases)
    - [Changelog](https://github.com/gitpython-developers/GitPython/blob/main/CHANGES)
    - [Commits](https://github.com/gitpython-developers/GitPython/compare/3.1.37...3.1.41)
    ---
    updated-dependencies:
2024-01-11 Bump jinja2 from 3.1.2 to 3.1.3
    Bumps [jinja2](https://github.com/pallets/jinja) from 3.1.2 to 3.1.3.
    - [Release notes](https://github.com/pallets/jinja/releases)
    - [Changelog](https://github.com/pallets/jinja/blob/main/CHANGES.rst)
    - [Commits](https://github.com/pallets/jinja/compare/3.1.2...3.1.3)
    ---
    updated-dependencies:
2024-01-29 Bump black from 23.12.1 to 24.1.1
    Bumps [black](https://github.com/psf/black) from 23.12.1 to 24.1.1.
    - [Release notes](https://github.com/psf/black/releases)
    - [Changelog](https://github.com/psf/black/blob/main/CHANGES.md)
    - [Commits](https://github.com/psf/black/compare/23.12.1...24.1.1)
    ---
    updated-dependencies:
2024-01-29 Bump pytest from 7.4.3 to 8.0.0
    Bumps [pytest](https://github.com/pytest-dev/pytest) from 7.4.3 to 8.0.0.
    - [Release notes](https://github.com/pytest-dev/pytest/releases)
    - [Changelog](https://github.com/pytest-dev/pytest/blob/main/CHANGELOG.rst)
    - [Commits](https://github.com/pytest-dev/pytest/compare/7.4.3...8.0.0)
    ---
    updated-dependencies:
2024-02-06 Bump cryptography from 41.0.6 to 42.0.0
    Bumps [cryptography](https://github.com/pyca/cryptography) from 41.0.6 to 42.0.0.
    - [Changelog](https://github.com/pyca/cryptography/blob/main/CHANGELOG.rst)
    - [Commits](https://github.com/pyca/cryptography/compare/41.0.6...42.0.0)
    ---
    updated-dependencies:
    - dependency-name: cryptography
2024-02-17 Bump cryptography from 41.0.6 to 42.0.2
    Bumps [cryptography](https://github.com/pyca/cryptography) from 41.0.6 to 42.0.2.
    - [Changelog](https://github.com/pyca/cryptography/blob/main/CHANGELOG.rst)
    - [Commits](https://github.com/pyca/cryptography/compare/41.0.6...42.0.2)
    ---
    updated-dependencies:
    - dependency-name: cryptography
2024-02-19 Bump pytest from 8.0.0 to 8.0.1
    Bumps [pytest](https://github.com/pytest-dev/pytest) from 8.0.0 to 8.0.1.
    - [Release notes](https://github.com/pytest-dev/pytest/releases)
    - [Changelog](https://github.com/pytest-dev/pytest/blob/main/CHANGELOG.rst)
    - [Commits](https://github.com/pytest-dev/pytest/compare/8.0.0...8.0.1)
    ---
    updated-dependencies:
2024-02-19 Bump black from 24.1.1 to 24.2.0
    Bumps [black](https://github.com/psf/black) from 24.1.1 to 24.2.0.
    - [Release notes](https://github.com/psf/black/releases)
    - [Changelog](https://github.com/psf/black/blob/main/CHANGES.md)
    - [Commits](https://github.com/psf/black/compare/24.1.1...24.2.0)
    ---
    updated-dependencies:
2024-02-21 Bump cryptography from 41.0.6 to 42.0.4
    Bumps [cryptography](https://github.com/pyca/cryptography) from 41.0.6 to 42.0.4.
    - [Changelog](https://github.com/pyca/cryptography/blob/main/CHANGELOG.rst)
    - [Commits](https://github.com/pyca/cryptography/compare/41.0.6...42.0.4)
    ---
    updated-dependencies:
    - dependency-name: cryptography
2024-02-26 Bump pylint from 3.0.3 to 3.1.0
    Bumps [pylint](https://github.com/pylint-dev/pylint) from 3.0.3 to 3.1.0.
    - [Release notes](https://github.com/pylint-dev/pylint/releases)
    - [Commits](https://github.com/pylint-dev/pylint/compare/v3.0.3...v3.1.0)
    ---
    updated-dependencies:
    - dependency-name: pylint
2024-02-26 Bump pytest from 8.0.0 to 8.0.2
    Bumps [pytest](https://github.com/pytest-dev/pytest) from 8.0.0 to 8.0.2.
    - [Release notes](https://github.com/pytest-dev/pytest/releases)
    - [Changelog](https://github.com/pytest-dev/pytest/blob/main/CHANGELOG.rst)
    - [Commits](https://github.com/pytest-dev/pytest/compare/8.0.0...8.0.2)
    ---
    updated-dependencies:
2024-03-04 Bump pytest from 8.0.0 to 8.1.0
    Bumps [pytest](https://github.com/pytest-dev/pytest) from 8.0.0 to 8.1.0.
    - [Release notes](https://github.com/pytest-dev/pytest/releases)
    - [Changelog](https://github.com/pytest-dev/pytest/blob/main/CHANGELOG.rst)
    - [Commits](https://github.com/pytest-dev/pytest/compare/8.0.0...8.1.0)
    ---
    updated-dependencies:
2024-03-11 Bump pytest from 8.0.0 to 8.1.1
    Bumps [pytest](https://github.com/pytest-dev/pytest) from 8.0.0 to 8.1.1.
    - [Release notes](https://github.com/pytest-dev/pytest/releases)
    - [Changelog](https://github.com/pytest-dev/pytest/blob/main/CHANGELOG.rst)
    - [Commits](https://github.com/pytest-dev/pytest/compare/8.0.0...8.1.1)
    ---
    updated-dependencies:
2024-03-18 Bump black from 24.1.1 to 24.3.0
    Bumps [black](https://github.com/psf/black) from 24.1.1 to 24.3.0.
    - [Release notes](https://github.com/psf/black/releases)
    - [Changelog](https://github.com/psf/black/blob/main/CHANGES.md)
    - [Commits](https://github.com/psf/black/compare/24.1.1...24.3.0)
    ---
    updated-dependencies:
2024-04-12 Bump idna from 3.4 to 3.7
    Bumps [idna](https://github.com/kjd/idna) from 3.4 to 3.7.
    - [Release notes](https://github.com/kjd/idna/releases)
    - [Changelog](https://github.com/kjd/idna/blob/master/HISTORY.rst)
    - [Commits](https://github.com/kjd/idna/compare/v3.4...v3.7)
    ---
    updated-dependencies:
2024-04-15 Bump black from 24.1.1 to 24.4.0
    Bumps [black](https://github.com/psf/black) from 24.1.1 to 24.4.0.
    - [Release notes](https://github.com/psf/black/releases)
    - [Changelog](https://github.com/psf/black/blob/main/CHANGES.md)
    - [Commits](https://github.com/psf/black/compare/24.1.1...24.4.0)
    ---
    updated-dependencies:
2024-04-25 Bump pydantic from 1.10.9 to 1.10.13
    Bumps [pydantic](https://github.com/pydantic/pydantic) from 1.10.9 to 1.10.13.
    - [Release notes](https://github.com/pydantic/pydantic/releases)
    - [Changelog](https://github.com/pydantic/pydantic/blob/main/HISTORY.md)
    - [Commits](https://github.com/pydantic/pydantic/compare/v1.10.9...v1.10.13)
    ---
    updated-dependencies:
2024-04-29 Bump black from 24.1.1 to 24.4.2
    Bumps [black](https://github.com/psf/black) from 24.1.1 to 24.4.2.
    - [Release notes](https://github.com/psf/black/releases)
    - [Changelog](https://github.com/psf/black/blob/main/CHANGES.md)
    - [Commits](https://github.com/psf/black/compare/24.1.1...24.4.2)
    ---
    updated-dependencies:
2024-04-29 Bump pytest from 8.0.0 to 8.2.0
    Bumps [pytest](https://github.com/pytest-dev/pytest) from 8.0.0 to 8.2.0.
    - [Release notes](https://github.com/pytest-dev/pytest/releases)
    - [Changelog](https://github.com/pytest-dev/pytest/blob/main/CHANGELOG.rst)
    - [Commits](https://github.com/pytest-dev/pytest/compare/8.0.0...8.2.0)
    ---
    updated-dependencies:
2024-05-03 Bump tqdm from 4.65.0 to 4.66.3
    Bumps [tqdm](https://github.com/tqdm/tqdm) from 4.65.0 to 4.66.3.
    - [Release notes](https://github.com/tqdm/tqdm/releases)
    - [Commits](https://github.com/tqdm/tqdm/compare/v4.65.0...v4.66.3)
    ---
    updated-dependencies:
    - dependency-name: tqdm
